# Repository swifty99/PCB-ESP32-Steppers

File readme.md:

# PCB-ESP32-Stepper

## Description

This project features a **PCB design for ESP32 development boards** (DevKit). It is designed to host ESP32 boards and provides a robust platform for controlling stepper motors. The PCB includes two slots for stepper motor drivers, supporting both simple drivers and more advanced ones such as **Fysetc Trinamic drivers**. Additionally, the board offers extra connectors for **I2C** or general-purpose **IOs**.

For control, the board is compatible with **FluidNC** firmware, which is a great solution for CNC machines and other motion control applications.

### Project Images

#### 3D Screenshot of the PCB

This 3D view shows the layout and components of the PCB design in KiCad.

#### Real Picture of the PCB

Some prototypes. The final version is better but not yet produces

---

## Features

- **ESP32 DevKit** support for easy integration with ESP32 microcontrollers.
- **Two stepper driver slots**, compatible with:
  - Simple stepper drivers (e.g., A4988, DRV8825).
  - Advanced **Fysetc Trinamic drivers**.
- Additional **I2C** and **IO** connectors for extra peripherals.
- Two MosFETs for switching high power devices.
- Power supply support for up to **28V** (requires a mini DC-DC converter to be soldered onto the board).
- Compatible with **FluidNC** firmware for motion control applications.
- Or use with ESPHome with custom component from [SlimCDK](https://github.com/slimcdk/esphome-custom-components)

---

## Schematic and PCB

The schematic and PCB design files were created using **KiCad** and can be found [here](https://github.com/your-repository-link).

---

## Required Hardware

1. **ESP32 DevKit board** (e.g., ESP32 DevKit v1).
2. **Mini DC-DC converter** for power supply (up to 28V) – ensure you solder this onto the board for proper functionality.
3. **Stepper motor drivers**:
   - Basic drivers: A4988, DRV8825, etc.
   - Advanced drivers: Fysetc Trinamic drivers (e.g., TMC2209, TMC2208).
4. **Stepper motors** for controlling motion.
5. XT30 plug for solid power Supply

---

## Software

For controlling the board, **FluidNC** is recommended. FluidNC is open-source firmware designed for CNC machines and motion control projects. It supports various motion control features and is easy to configure for your specific needs.

- **FluidNC Firmware**: [FluidNC](http://wiki.fluidnc.com)

---

## Assembly Instructions

1. **Solder the Mini DC-DC Converter**: You need to solder a mini DC-DC converter onto the board to provide power to the system (up to 28V input).
2. **Install ESP32 DevKit**: Place your ESP32 DevKit board into the designated slot.
3. **Insert Stepper Drivers**: Insert your preferred stepper drivers into the two available slots.
4. **Connect Peripherals**: Use the additional I2C or IO connectors to integrate sensors, displays, or other components as needed.

---

## License

This project is licensed under the **MIT License**. See the `LICENSE` file for more details.

---

## Contact

For any questions or support, feel free to contact me at [your-email@example.com].

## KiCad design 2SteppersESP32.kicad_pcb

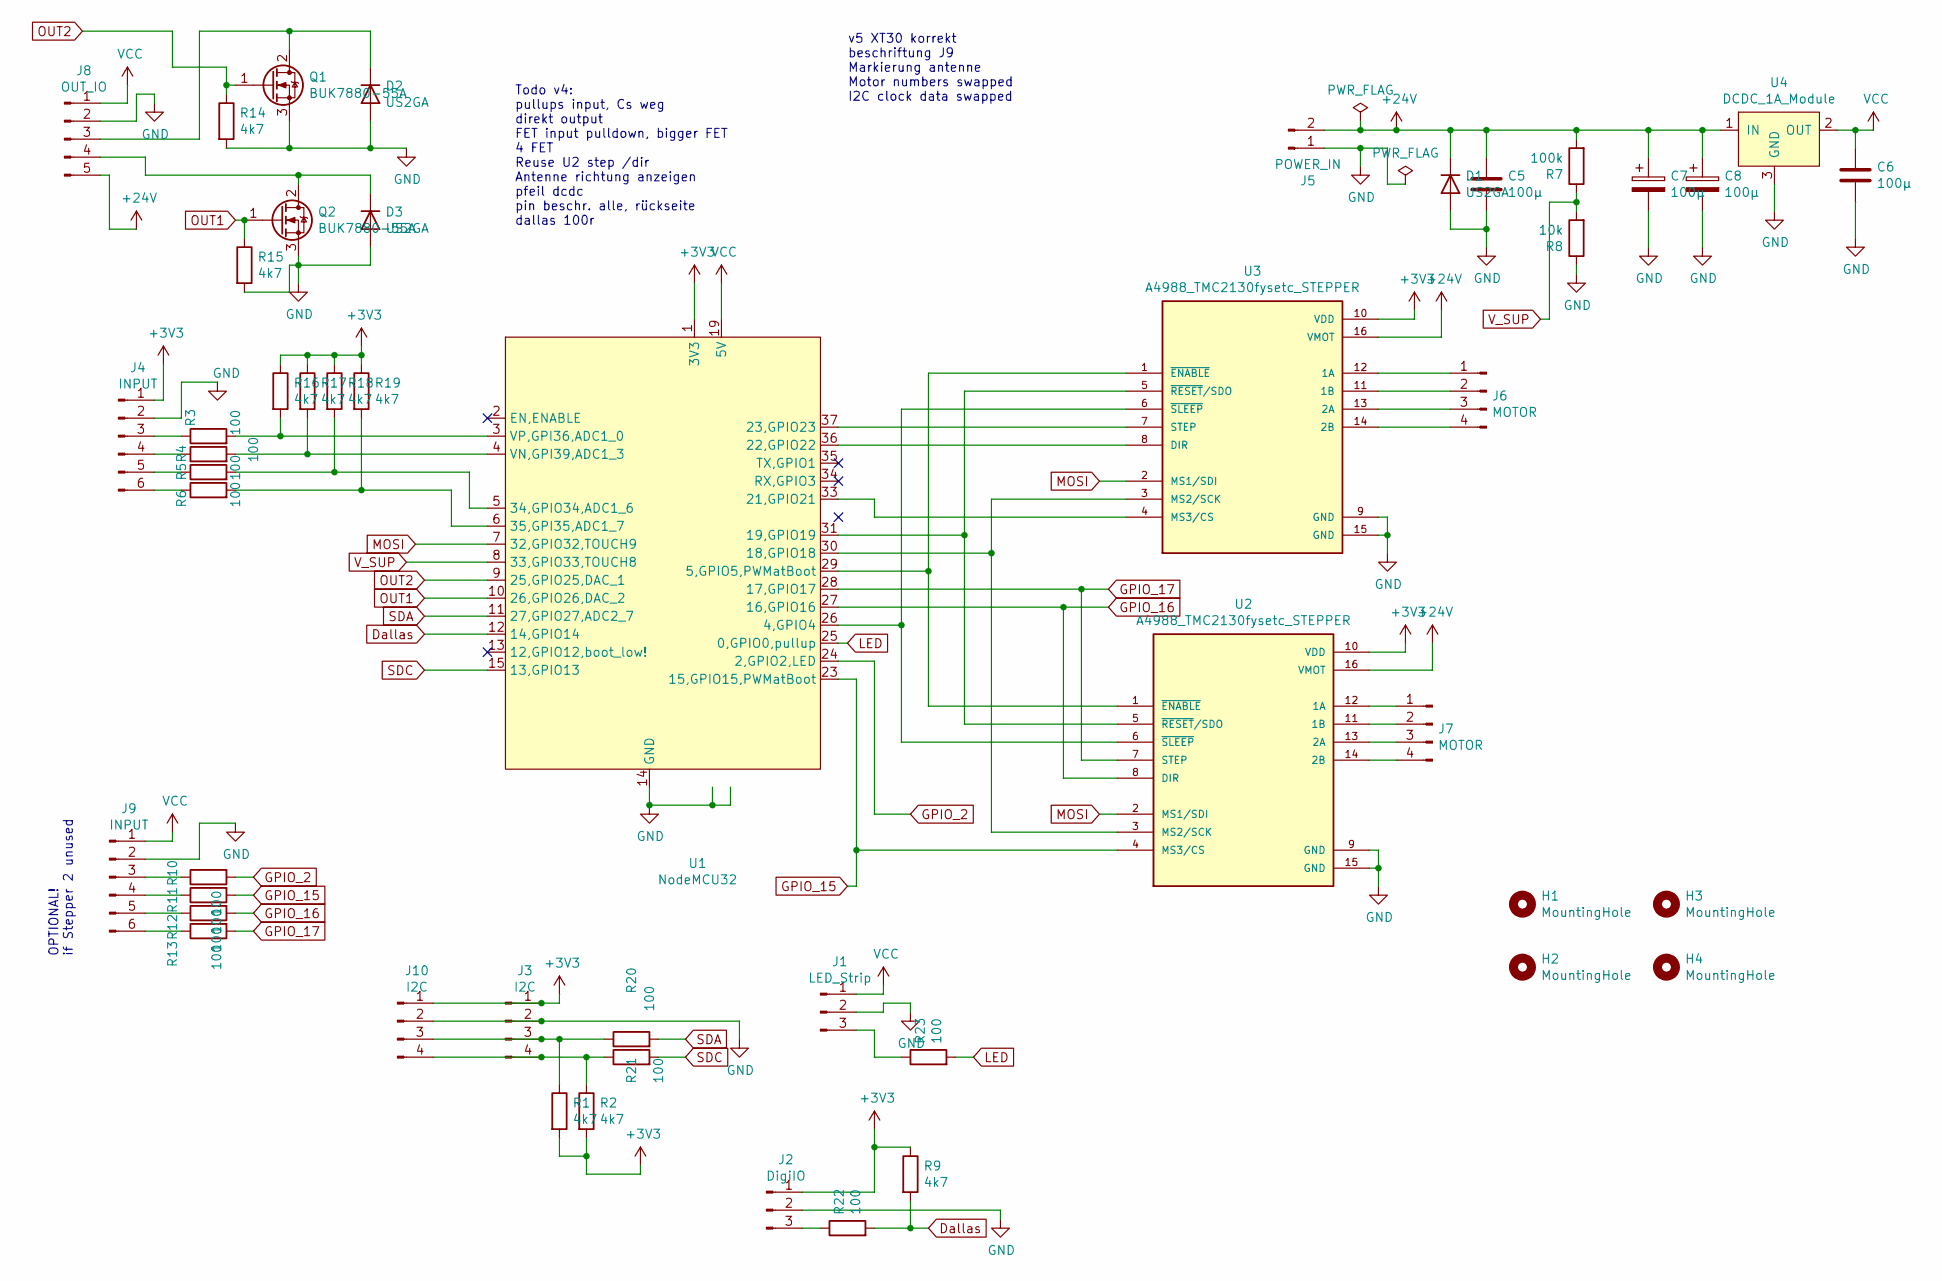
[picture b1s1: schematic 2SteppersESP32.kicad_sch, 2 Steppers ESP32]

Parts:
C5, C6: 100µ; C_1206_3216Metric
C7, C8: 100µ; CP_Elec_10x10
D1, D2, D3: US2GA; D_SMA
H1, H2, H3, H4: MountingHole; MountingHole_4.3mm_M4_Pad
J1: LED_Strip; JST_XH_B3B-XH-A_1x03_P2.50mm_Vertical
J2: DigiIO; JST_XH_B3B-XH-A_1x03_P2.50mm_Vertical
J3, J10: I2C; JST_XH_B4B-XH-A_1x04_P2.50mm_Vertical
J4: INPUT; JST_XH_S6B-XH-A_1x06_P2.50mm_Horizontal
J5: POWER_IN; AMASS_XT30U-F_1x02_P5.0mm_Vertical
J6, J7: MOTOR; JST_XH_B4B-XH-A_1x04_P2.50mm_Vertical
J8: OUT_IO; JST_XH_B5B-XH-A_1x05_P2.50mm_Vertical
J9: INPUT; JST_XH_B6B-XH-A_1x06_P2.50mm_Vertical
Q1, Q2: BUK7880-55A; SOT-223-3_TabPin2
R1, R2, R9, R14, R15, R16, R17, R18, R19: 4k7; R_0805_2012Metric
R3, R4, R5, R6, R10, R11, R12, R13, R20, R21, R22, R23: 100; R_0805_2012Metric
R7: 100k; R_0805_2012Metric
R8: 10k; R_0805_2012Metric
U1: NodeMCU32; ESP32_NODEMCU
U2, U3: A4988_TMC2130fysetc_STEPPER; MODULE_A4988_TMC2130_STEPPER
U4: DCDC_1A_Module; DCDC_1A_module

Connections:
+3V3: J2.1, J3.1, J4.1, J10.1, R1.2, R2.2, R9.1, R16.1, R17.1, R18.1, R19.1, U1.1 (3V3), U2.10 (VDD), U3.10 (VDD)
+24V: C5.1, C7.1, C8.1, D1.1 (K), J5.2, J8.5, R7.2, U2.16 (VMOT), U3.16 (VMOT), U4.1 (IN)
Dallas: R9.2, R22.2, U1.12 (14,GPIO14)
GND: C5.2, C6.2, C7.2, C8.2, D1.2 (A), D2.2 (A), D3.2 (A), J1.2, J2.2, J3.2, J4.2, J5.1, J8.2, J9.2, J10.2, Q1.3 (S), Q2.3 (S), R8.1, R14.2, R15.2, U1.14 (GND), U1.38 (GND), U2.9 (GND), U2.15 (GND), U3.9 (GND), U3.15 (GND), U4.3 (GND)
GPIO_2: R10.2, U1.24 (2,GPIO2,LED)
GPIO_15: R11.2, U1.23 (15,GPIO15,PWMatBoot), U2.4 (MS3/CS)
GPIO_16: R12.2, U1.27 (16,GPIO16), U2.8 (DIR)
GPIO_17: R13.2, U1.28 (17,GPIO17), U2.7 (STEP)
LED: R23.2, U1.25 (0,GPIO0,pullup)
MOSI: U1.7 (32,GPIO32,TOUCH9), U2.2 (MS1/SDI), U3.2 (MS1/SDI)
unnamed: D2.1 (K), J8.3, Q1.2 (D)
unnamed: D3.1 (K), J8.4, Q2.2 (D)
unnamed: J1.3, R23.1
unnamed: J2.3, R22.1
unnamed: J4.3, R3.1
unnamed: J4.4, R4.1
unnamed: J4.5, R5.1
unnamed: J4.6, R6.1
unnamed: J6.1, U3.12 (1A)
unnamed: J6.2, U3.11 (1B)
unnamed: J6.3, U3.13 (2A)
unnamed: J6.4, U3.14 (2B)
unnamed: J7.1, U2.12 (1A)
unnamed: J7.2, U2.11 (1B)
unnamed: J7.3, U2.13 (2A)
unnamed: J7.4, U2.14 (2B)
unnamed: J9.3, R10.1
unnamed: J9.4, R11.1
unnamed: J9.5, R12.1
unnamed: J9.6, R13.1
unnamed: J3.3, J10.3, R1.1, R20.1
unnamed: J3.4, J10.4, R2.1, R21.1
unnamed: R3.2, R16.2, U1.3 (VP,GPI36,ADC1_0)
unnamed: R4.2, R17.2, U1.4 (VN,GPI39,ADC1_3)
unnamed: R5.2, R18.2, U1.5 (34,GPIO34,ADC1_6)
unnamed: R6.2, R19.2, U1.6 (35,GPI35,ADC1_7)
unnamed: U1.26 (4,GPIO4), U2.6 (~SLEEP), U3.6 (~SLEEP)
unnamed: U1.29 (5,GPIO5,PWMatBoot), U2.1 (~ENABLE), U3.1 (~ENABLE)
unnamed: U1.30 (18,GPIO18), U2.3 (MS2/SCK), U3.3 (MS2/SCK)
unnamed: U1.31 (19,GPIO19), U2.5 (~RESET/SDO), U3.5 (~RESET/SDO)
unnamed: U1.33 (21,GPIO21), U3.4 (MS3/CS)
unnamed: U1.36 (22,GPIO22), U3.8 (DIR)
unnamed: U1.37 (23,GPIO23), U3.7 (STEP)
OUT1: Q2.1 (G), R15.1, U1.10 (26,GPIO26,DAC_2)
OUT2: Q1.1 (G), R14.1, U1.9 (25,GPIO25,DAC_1)
SDA: R21.2, U1.15 (13,GPIO13)
SDC: R20.2, U1.11 (27,GPIO27,ADC2_7)
VCC: C6.1, J1.1, J8.1, J9.1, U1.19 (5V), U4.2 (OUT)
V_SUP: R7.1, R8.2, U1.8 (33,GPIO33,TOUCH8)

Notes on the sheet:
v5 XT30 korrekt beschriftung J9 Markierung antenne Motor numbers swapped I2C clock data swapped
Todo v4: pullups input, Cs weg direkt output FET input pulldown, bigger FET 4 FET Reuse U2 step /dir Antenne richtung anzeigen pfeil dcdc pin beschr. alle, rückseite dallas 100r
OPTIONAL! if Stepper 2 unused

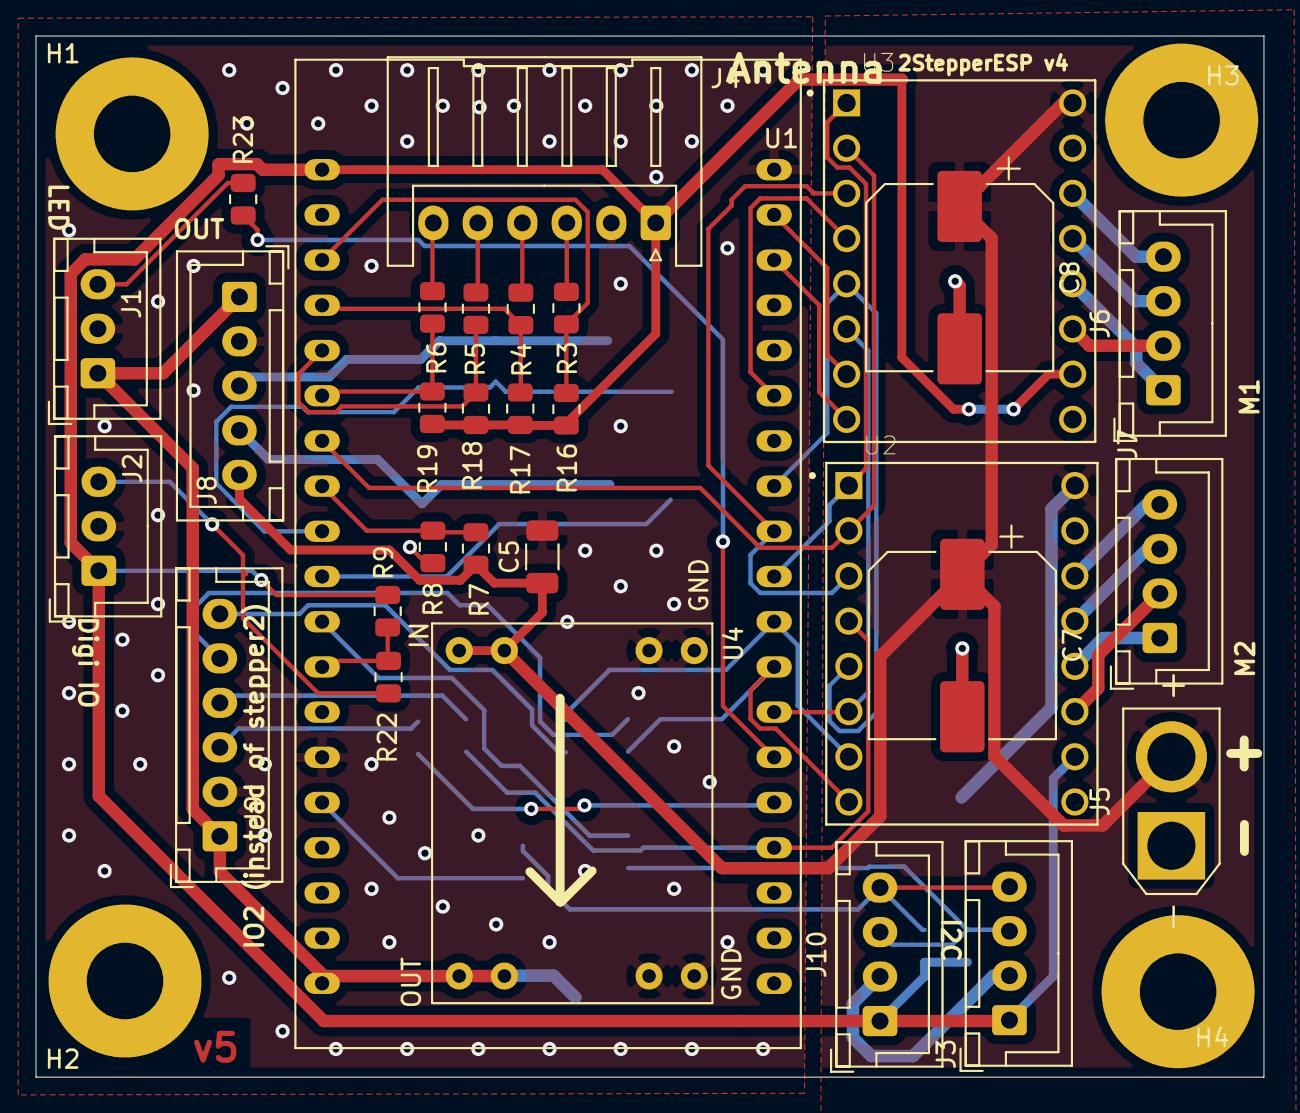
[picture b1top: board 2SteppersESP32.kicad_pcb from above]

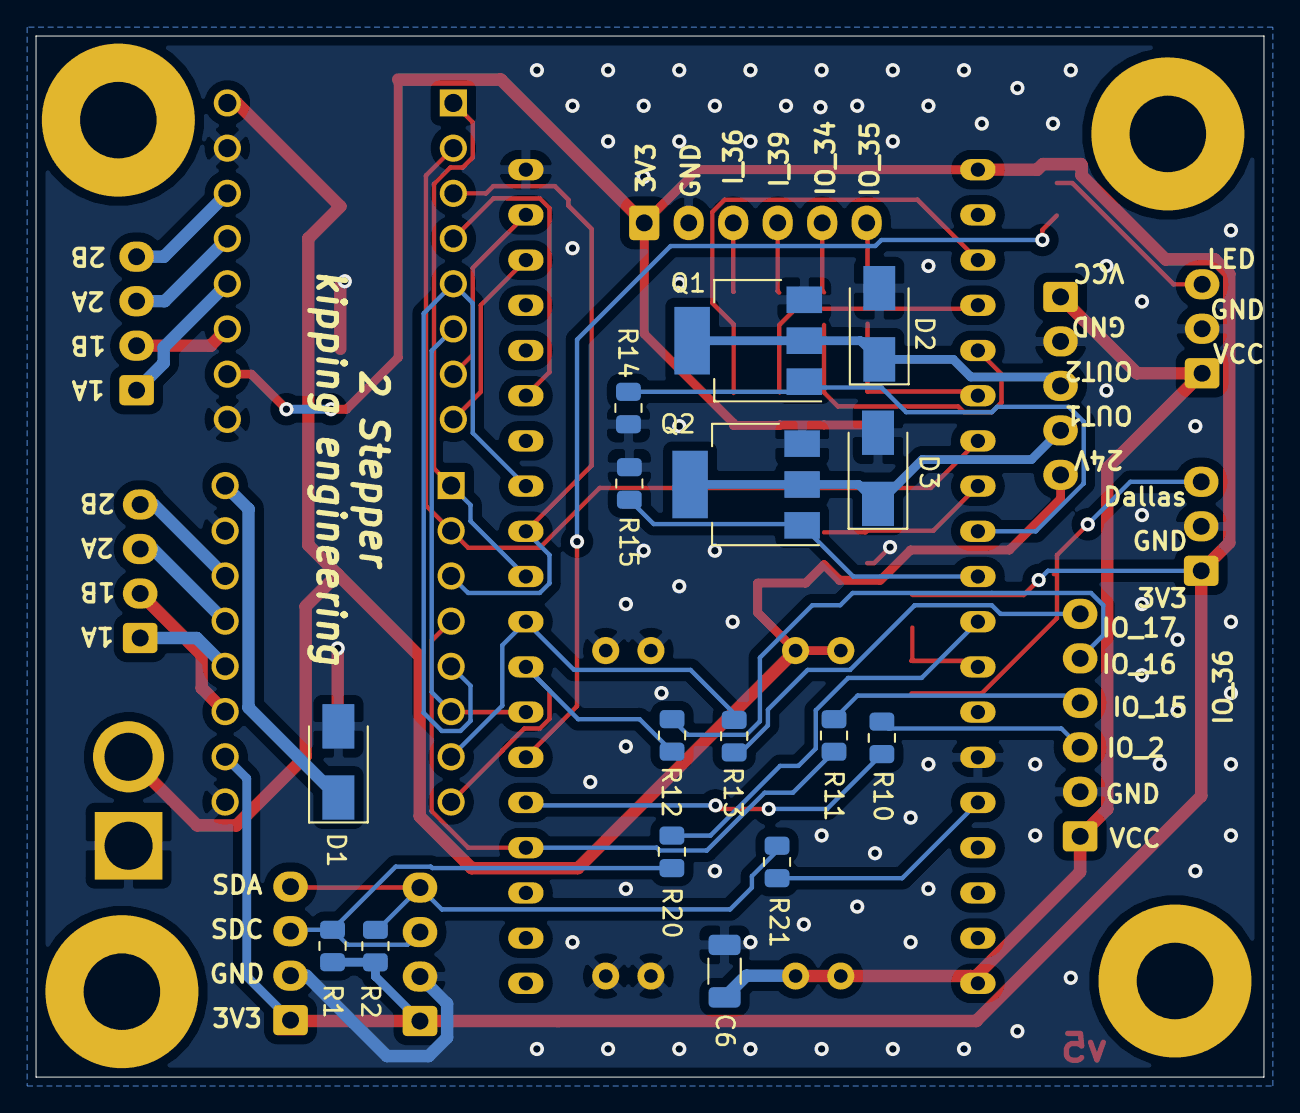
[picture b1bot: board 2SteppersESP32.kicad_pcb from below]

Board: 2 copper layers, 69.0 x 58.5 mm, 50 parts (16 on the bottom side), 49 nets.

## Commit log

2025-01-26 Initial commit for KiCad project
2025-01-26 pcb upate
2025-01-26 pcb images
2025-01-26 Rename pcb prototypes.jpeg to pcb_prototypes.jpeg
